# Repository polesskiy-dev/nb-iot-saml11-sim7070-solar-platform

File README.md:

# NB IoT platform

### Based on:
* MCU: Microchip SAML11
* GSM, GPS: SIMCom SIM7070
* Power: 2V Solar panel or DC 5V, MPPT harvester, 1xLiFePO4 18650 

### Hardware features:
* Sensors IN: 
  * 2xPulse, 3V3-48V tolerant, optocouple galvanic isolation. Supports NPN, PNP
  * 1xADC, 1V2-48V tolerant
  * 2x4 wires: USART, LIN client, I2C client/host, SPI client/host, RS485 (3V3), 3V3-5V tolerant, buffered
* Sensors power OUT: 3V3, 12V or self-powered
* Power: 1V5-2V5 Solar MPPT Harvester or DC 5V, LiFePO4/Li-ion charger, reverse polarity protection
* [ ] power consumption values plot

### Software features:
* [ ] AWS integration
* [ ] MQTTs
* [ ] I2C BME280 temperature/humidity/pressure sensor support

### Schematics:

### Board:

### Enclosure:
Gainta G113

### BOM:
[Interactive BOM](https://polesskiy-dev.github.io/nb-iot-saml11-sim7070-solar-platform/bom/ibom.html)

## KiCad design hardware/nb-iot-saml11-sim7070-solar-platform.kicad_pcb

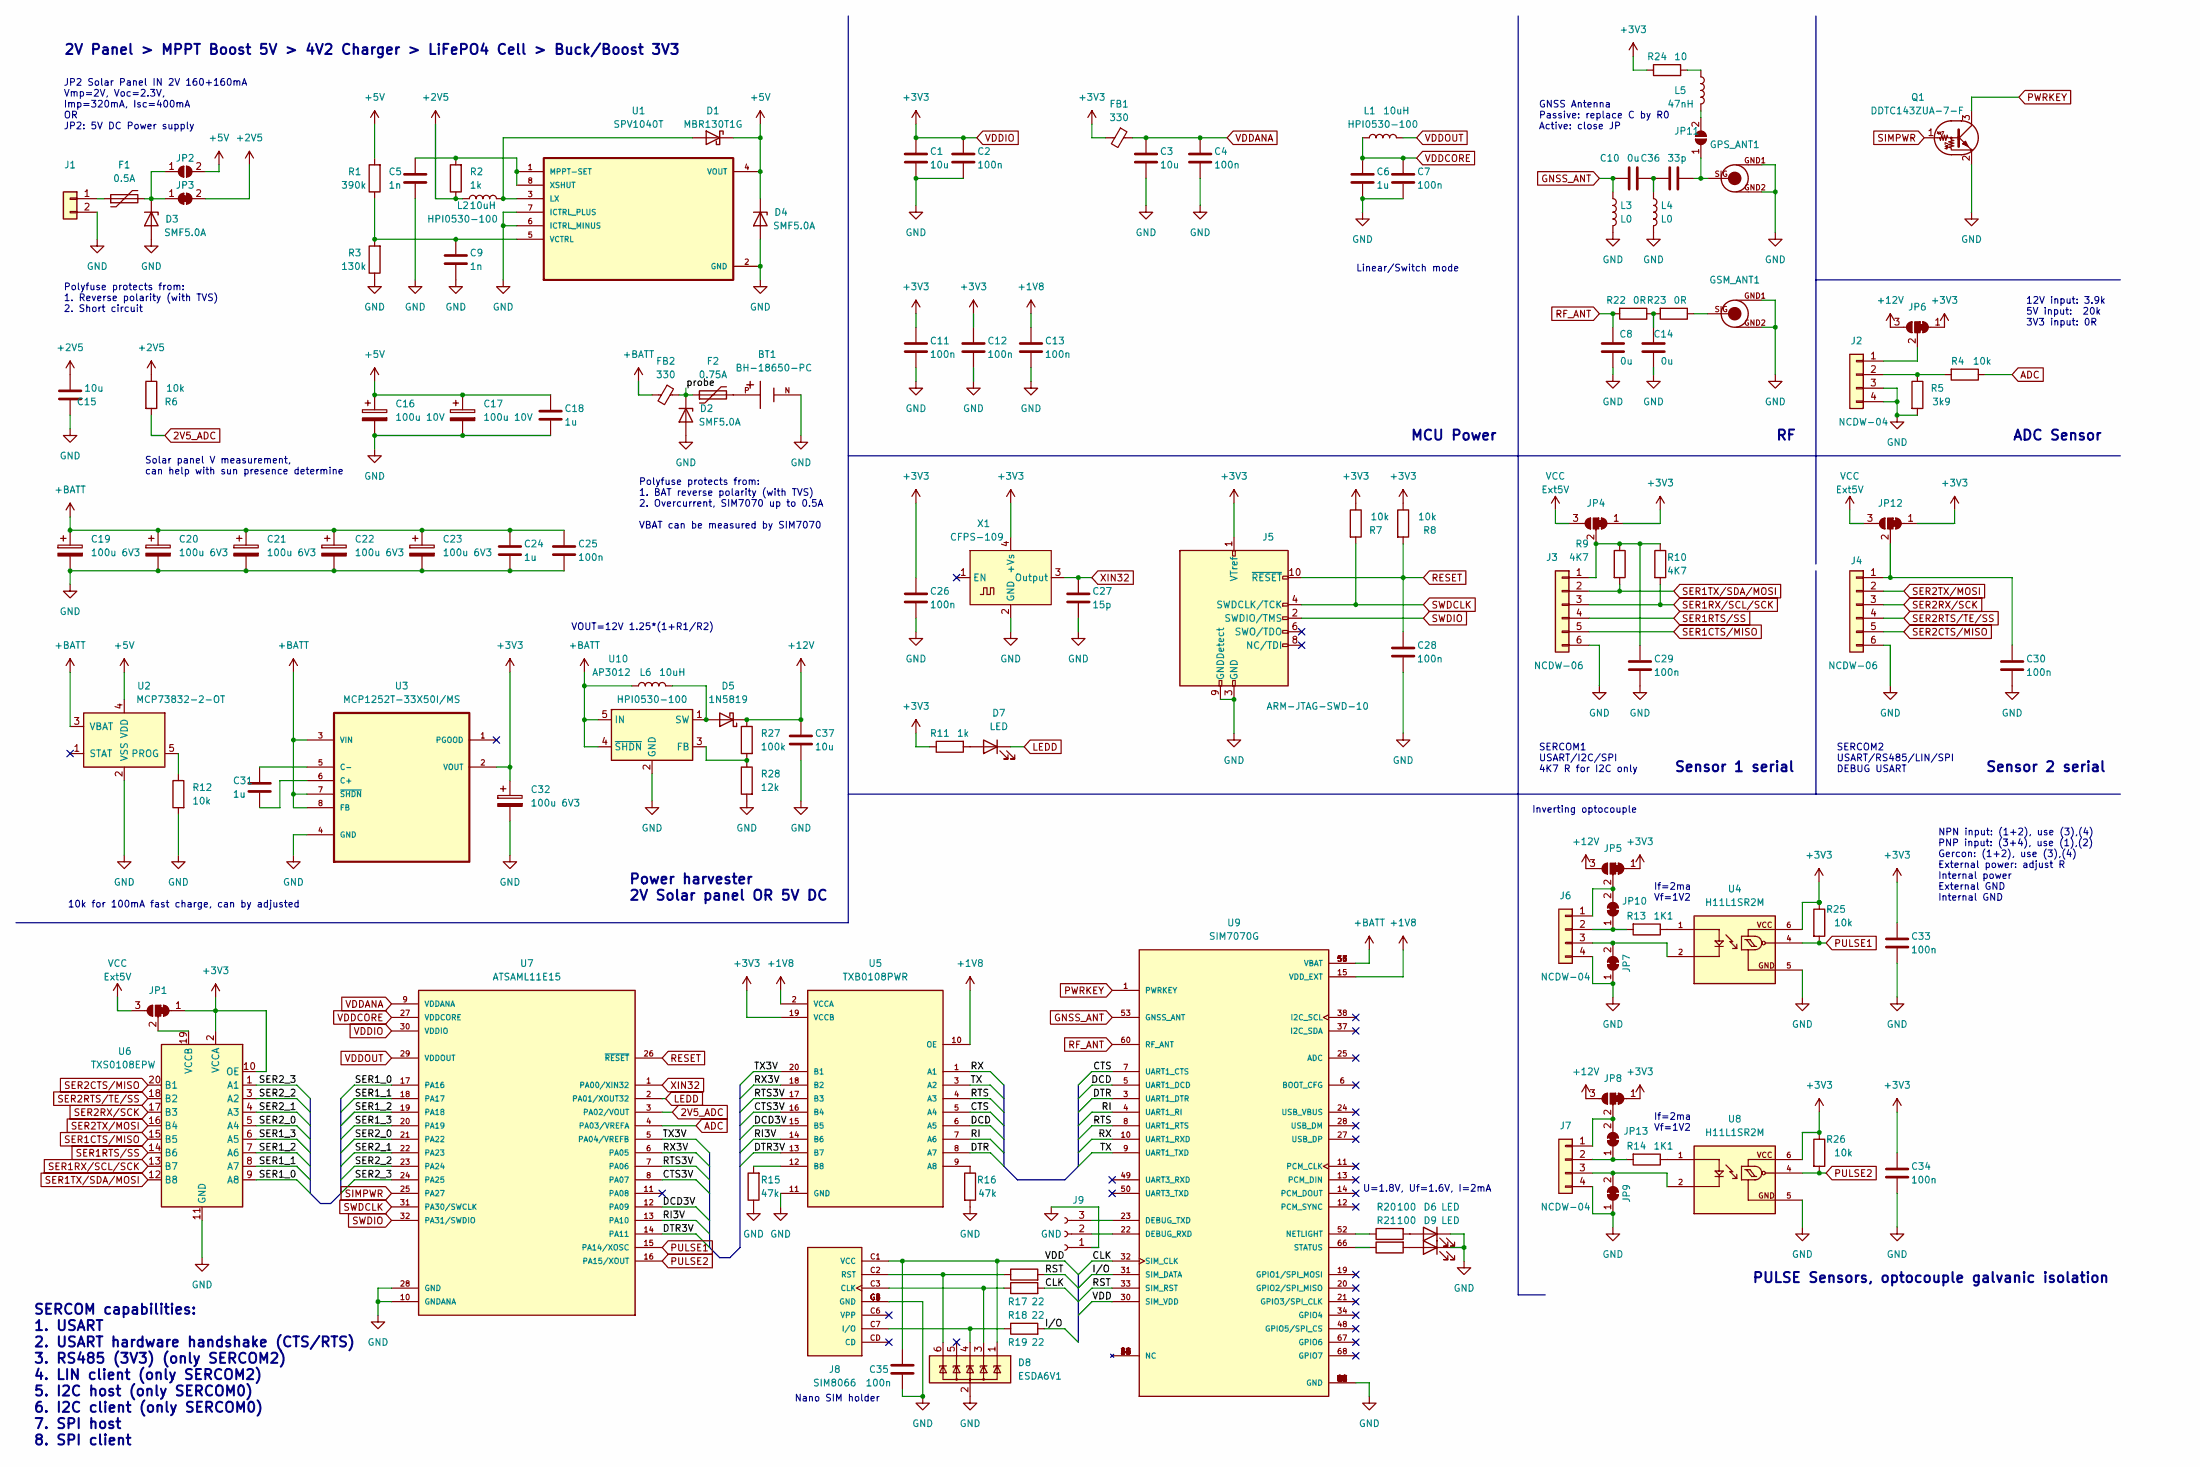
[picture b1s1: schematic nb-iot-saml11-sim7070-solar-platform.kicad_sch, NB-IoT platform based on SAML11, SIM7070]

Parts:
BT1: BH-18650-PC; BAT_BH-18650-PC; PARTREV 05/17/19
C1, C3, C15, C37: 10u; C_0805_2012Metric_Pad1.18x1.45mm_HandSolder
C2, C4, C7, C11, C12, C13, C25, C26, C28, C29, C30, C33, C34, C35: 100n; C_0805_2012Metric_Pad1.18x1.45mm_HandSolder
C5, C9: 1n; C_0805_2012Metric_Pad1.18x1.45mm_HandSolder
C6, C18, C24, C31: 1u; C_0805_2012Metric_Pad1.18x1.45mm_HandSolder
C8, C10, C14: 0u; C_0603_1608Metric_Pad1.08x0.95mm_HandSolder
C16, C17: 100u 10V; CP_EIA-7343-31_Kemet-D_Pad2.25x2.55mm_HandSolder; PARTNUMBER T491D107K010AT
C19, C20, C21, C22, C23, C32: 100u 6V3; CP_EIA-3528-21_Kemet-B_Pad1.50x2.35mm_HandSolder; PARTNUMBER TAJB107K006RNJ
C27: 15p; C_0805_2012Metric_Pad1.18x1.45mm_HandSolder
C36: 33p; C_0603_1608Metric_Pad1.08x0.95mm_HandSolder
D1: D_Schottky; D_SOD-123; PARTNUMBER MBR130T1G
D2, D3, D4: D_Zener; D_SOD-123; PARTNUMBER SMF5.0A
D5: 1N5819; D_SOD-123
D6, D7, D9: LED; LED_0805_2012Metric_Pad1.15x1.40mm_HandSolder
D8: ESDA6V1; SOT-23-6
F1: 0.5A; Fuse_1206_3216Metric_Pad1.42x1.75mm_HandSolder; PARTNUMBER SMD1206P050TF
F2: 0.75A; Fuse_2920_7451Metric_Pad2.10x5.45mm_HandSolder; PARTNUMBER 0ZCF0075FF2C
FB1, FB2: 330; R_0805_2012Metric_Pad1.20x1.40mm_HandSolder
GPS_ANT1: U.FL-R-SMT-1; GHI-CONNECTORS_U.FL-R-SMT-1
GSM_ANT1: U.FL-R-SMT-1; GHI-CONNECTORS_U.FL-R-SMT-1
J1: Conn_01x02; Molex_SL_171971-0002_1x02_P2.54mm_Vertical
J2, J6, J7: NCDW-04; Molex_SL_171971-0004_1x04_P2.54mm_Vertical
J3, J4: NCDW-06; Molex_SL_171971-0006_1x06_P2.54mm_Vertical
J5: ARM-JTAG-SWD-10; PinHeader_2x05_P2.54mm_Vertical
J8: SIM8066; GCT_SIM8066-6-1-14-01-A_REVA; PARTREV REVA
J9: Conn_01x03_Female; PinHeader_1x03_P2.54mm_Vertical
JP1, JP4, JP5, JP6, JP8, JP12: SolderJumper_3_Bridged12; SolderJumper-3_P1.3mm_Bridged12_RoundedPad1.0x1.5mm_NumberL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
JP2, JP11: SolderJumper_2_Open; SolderJumper-2_P1.3mm_Open_RoundedPad1.0x1.5mm
JP3, JP7, JP9, JP10, JP13: SolderJumper_2_Bridged; SolderJumper-2_P1.3mm_Bridged_RoundedPad1.0x1.5mm
L1, L2, L6: 10uH; L_Taiyo-Yuden_MD-5050; PARTNUMBER HPI0530-100
L3, L4: L0; L_0603_1608Metric_Pad1.05x0.95mm_HandSolder
L5: 47nH; L_0603_1608Metric_Pad1.05x0.95mm_HandSolder
Q1: DDTC143ZUA-7-F; SOT-323_SC-70_Handsoldering
R1: 390k; R_0805_2012Metric_Pad1.20x1.40mm_HandSolder
R2, R11: 1k; R_0805_2012Metric_Pad1.20x1.40mm_HandSolder
R3: 130k; R_0805_2012Metric_Pad1.20x1.40mm_HandSolder
R4, R6, R7, R8, R12, R25, R26: 10k; R_0805_2012Metric_Pad1.20x1.40mm_HandSolder
R5: 3k9; R_0805_2012Metric_Pad1.20x1.40mm_HandSolder
R9, R10: 4K7; R_0805_2012Metric_Pad1.20x1.40mm_HandSolder
R13, R14: 1K1; R_0805_2012Metric_Pad1.20x1.40mm_HandSolder
R15, R16: 47k; R_0805_2012Metric_Pad1.20x1.40mm_HandSolder
R17, R18, R19: 22; R_0805_2012Metric_Pad1.20x1.40mm_HandSolder
R20, R21: 100; R_0805_2012Metric_Pad1.20x1.40mm_HandSolder
R22, R23: 0R; R_0603_1608Metric_Pad0.98x0.95mm_HandSolder
R24: 10; R_0805_2012Metric_Pad1.20x1.40mm_HandSolder
R27: 100k; R_0805_2012Metric_Pad1.20x1.40mm_HandSolder
R28: 12k; R_0805_2012Metric_Pad1.20x1.40mm_HandSolder
U1: SPV1040T; TSSOP-8_4.4x3mm_P0.65mm; PARTREV 7
U2: MCP73832-2-OT; SOT-23-5_HandSoldering
U3: MCP1252T-33X50I/MS; MSOP-8_3x3mm_P0.65mm; MPN MCP1252T-33X50I/MS
U4, U8: H11L1SR2M; IC_H11L1SR2M; PARTREV 3
U5: TXB0108PWR; TSSOP-20_4.4x6.5mm_P0.65mm; PARTREV H
U6: TXS0108EPW; TSSOP-20_4.4x6.5mm_P0.65mm
U7: ATSAML11E15; TQFP-32_7x7mm_P0.8mm; PARTREV G
U9: SIM7070G; MODULE_SIM7070G; PARTREV V1.03
U10: AP3012; SOT-23-5
X1: CFPS-109

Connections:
2V5_ADC: R6.2, U7.3 (PA02/VOUT)
+1V8: C13.1, U5.2 (VCCA), U5.10 (OE), U9.15 (VDD_EXT)
+2V5: C15.2, JP3.2 (B), L2.1, R2.1, R6.1
+5V: C16.1, C17.1, C18.1, D1.1 (K), D4.1 (K), JP2.2 (B), R1.2, U1.4 (VOUT), U2.4 (VDD)
+12V: C37.1, D5.1 (K), JP5.3 (B), JP6.3 (B), JP8.3 (B), R27.1
+BATT: C19.1, C20.1, C21.1, C22.1, C23.1, C24.1, C25.1, FB2.2, L6.1, U2.3 (VBAT), U3.3 (VIN), U3.7 (~SHDN), U3.8 (FB), U9.55 (VBAT), U9.56 (VBAT), U9.57 (VBAT), U10.4 (~SHDN), U10.5 (IN)
/CLK: R18.2, U9.32 (SIM_CLK)
/CTS: U5.5 (A4), U9.7 (UART1_CTS)
/CTS3V: U5.16 (B4), U7.8 (PA07)
/DCD: U5.6 (A5), U9.5 (UART1_DCD)
/DCD3V: U5.15 (B5), U7.12 (PA09)
/DTR: U5.8 (A7), U9.3 (UART1_DTR)
/DTR3V: U5.13 (B7), U7.14 (PA11)
/I/O: R19.2, U9.31 (SIM_DATA)
/RI: U5.7 (A6), U9.4 (UART1_RI)
/RI3V: U5.14 (B6), U7.13 (PA10)
/RST: R17.2, U9.33 (SIM_RST)
/RTS: U5.4 (A3), U9.8 (UART1_RTS)
/RTS3V: U5.17 (B3), U7.7 (PA06)
/RX: U5.1 (A1), U9.10 (UART1_RXD)
/RX3V: U5.18 (B2), U7.6 (PA05)
/SER1_0: U6.9 (A8), U7.17 (PA16)
/SER1_1: U6.8 (A7), U7.18 (PA17)
/SER1_2: U6.7 (A6), U7.19 (PA18)
/SER1_3: U6.6 (A5), U7.20 (PA19)
/SER2_0: U6.5 (A4), U7.21 (PA22)
/SER2_1: U6.4 (A3), U7.22 (PA23)
/SER2_2: U6.3 (A2), U7.23 (PA24)
/SER2_3: U6.1 (A1), U7.24 (PA25)
/TX: U5.3 (A2), U9.9 (UART1_TXD)
/TX3V: U5.20 (B1), U7.5 (PA04/VREFB)
/VDD: C35.1, D8.1 (IO1), J8.C1 (VCC), U9.30 (SIM_VDD)
/probe: D2.1 (K), F2.1, FB2.1; also elsewhere on the board
ADC: R4.1, U7.4 (PA03/VREFA)
GND: BT1.N, C1.2, C2.2, C3.2, C4.2, C5.2, C6.2, C7.2, C8.1, C9.2, C11.2, C12.2, C13.2, C14.1, C15.1, C16.2, C17.2, C18.2, C19.2, C20.2, C21.2, C22.2, C23.2, C24.2, C25.2, C26.2, C27.2, C28.2, C29.2, C30.2, C32.2, C33.2, C34.2, C35.2, C37.2, D2.2 (A), D3.2 (A), D4.2 (A), D6.1 (K), D8.2 (GND), D9.1 (K), GPS_ANT1.GND1, GPS_ANT1.GND2, GSM_ANT1.GND1, GSM_ANT1.GND2, J1.2, J2.3, J2.4, J3.6, J4.6, J5.3 (GND), J5.5 (GND), J5.9 (GNDDetect), J6.4, J7.4, J8.C5 (GND), J8.G1 (GND), J8.G2 (GND), J8.G3 (GND), J8.G4 (GND), J9.1, JP7.1 (A), JP9.1 (A), L3.2, L4.2, Q1.2 (E), R3.1, R5.2, R12.2, R15.1, R16.2, R28.2, U1.2 (GND), U1.6 (ICTRL_MINUS), U1.7 (ICTRL_PLUS), U2.2 (VSS), U3.4 (GND), U4.5, U5.11 (GND), U6.11 (GND), U7.10 (GNDANA), U7.28 (GND), U8.5, U9.2 (GND), U9.17 (GND), U9.18 (GND), U9.29 (GND), U9.39 (GND), U9.45 (GND), U9.46 (GND), U9.54 (GND), U9.58 (GND), U9.59 (GND), U9.61 (GND), U9.62 (GND), U9.63 (GND), U9.64 (GND), U9.65 (GND), U10.2 (GND), X1.2 (GND); also elsewhere on the board
GNSS_ANT: C10.2, L3.1, U9.53 (GNSS_ANT)
LEDD: D7.1 (K), U7.2 (PA01/XOUT32)
unnamed: BT1.P, F2.2
unnamed: C5.1, R2.2, U1.1 (MPPT-SET), U1.8 (XSHUT)
unnamed: C9.1, R1.1, R3.2, U1.5 (VCTRL)
unnamed: C10.1, C36.2, L4.1
unnamed: C14.2, R22.1, R23.2
unnamed: C29.1, J3.1, JP4.2 (C), R9.1, R10.1
unnamed: C30.1, J4.1, JP12.2 (C)
unnamed: C31.1, U3.5 (C-)
unnamed: C31.2, U3.6 (C+)
unnamed: C36.1, GPS_ANT1.SIG, JP11.1 (A)
unnamed: D1.2 (A), L2.2, U1.3 (LX)
unnamed: D3.1 (K), F1.2, JP2.1 (A), JP3.1 (A)
unnamed: D5.2 (A), L6.2, U10.1 (SW)
unnamed: D6.2 (A), R20.2
unnamed: D7.2 (A), R11.2
unnamed: D8.3 (IO2), J8.C3 (CLK), R18.1
unnamed: D8.4 (IO3), J8.C7 (I/O), R19.1
unnamed: D8.6 (IO5), J8.C2 (RST), R17.1
unnamed: D9.2 (A), R21.2
unnamed: F1.1, J1.1
unnamed: GSM_ANT1.SIG, R23.1
unnamed: J2.1, JP6.2 (C)
unnamed: J2.2, R4.2, R5.1
unnamed: J6.1, JP5.2 (C), JP10.2 (B)
unnamed: J6.2, JP10.1 (A), R13.2
unnamed: J6.3, JP7.2 (B), U4.2
unnamed: J7.1, JP8.2 (C), JP13.2 (B)
unnamed: J7.2, JP13.1 (A), R14.2
unnamed: J7.3, JP9.2 (B), U8.2
unnamed: J9.2, U9.22 (DEBUG_RXD)
unnamed: J9.3, U9.23 (DEBUG_TXD)
unnamed: JP1.2 (C), U6.19 (VCCB)
unnamed: JP11.2 (B), L5.2
unnamed: L5.1, R24.2
unnamed: R12.1, U2.5 (PROG)
unnamed: R13.1, U4.1
unnamed: R14.1, U8.1
unnamed: R15.2, U5.12 (B8)
unnamed: R16.1, U5.9 (A8)
unnamed: R20.1, U9.52 (NETLIGHT)
unnamed: R21.1, U9.66 (STATUS)
unnamed: R27.2, R28.1, U10.3 (FB)
PULSE1: R25.2, U4.4, U7.15 (PA14/XOSC)
PULSE2: R26.2, U7.16 (PA15/XOUT), U8.4
PWRKEY: Q1.3 (C), U9.1 (PWRKEY)
RESET: C28.1, J5.10 (~RESET), R8.2, U7.26 (~RESET)
RF_ANT: C8.2, R22.2, U9.60 (RF_ANT)
SER1CTS/MISO: J3.5, U6.15 (B5)
SER1RTS/SS: J3.4, U6.14 (B6)
SER1RX/SCL/SCK: J3.3, R10.2, U6.13 (B7)
SER1TX/SDA/MOSI: J3.2, R9.2, U6.12 (B8)
SER2CTS/MISO: J4.5, U6.20 (B1)
SER2RTS/TE/SS: J4.4, U6.18 (B2)
SER2RX/SCK: J4.3, U6.17 (B3)
SER2TX/MOSI: J4.2, U6.16 (B4)
SIMPWR: Q1.1 (B), U7.25 (PA27)
SWDCLK: J5.4 (SWDCLK/TCK), R7.2, U7.31 (PA30/SWCLK)
SWDIO: J5.2 (SWDIO/TMS), U7.32 (PA31/SWDIO)
VCC: JP1.3 (B), JP4.3 (B), JP12.3 (B)
VDDANA: C3.1, C4.1, FB1.1, U7.9 (VDDANA)
VDDCORE: C6.1, C7.1, L1.1, U7.27 (VDDCORE)
VDDIO: C1.1, C2.1, C11.1, C12.1, C26.1, C32.1, C33.1, C34.1, FB1.2, J5.1 (VTref), JP1.1 (A), JP4.1 (A), JP5.1 (A), JP6.1 (A), JP8.1 (A), JP12.1 (A), R7.1, R8.1, R11.1, R24.1, R25.1, R26.1, U3.2 (VOUT), U4.6, U5.19 (VCCB), U6.2 (VCCA), U6.10 (OE), U7.30 (VDDIO), U8.6, X1.4 (+Vs)
VDDOUT: L1.2, U7.29 (VDDOUT)
XIN32: C27.1, U7.1 (PA00/XIN32), X1.3 (Output)

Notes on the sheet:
If=2ma Vf=1V2
ADC Sensor
Polyfuse protects from: 1. BAT reverse polarity (with TVS) 2. Overcurrent, SIM7070 up to 0.5A VBAT can be measured by SIM7070
GNSS Antenna Passive: replace C by R0 Active: close JP
10k for 100mA fast charge, can by adjusted
U=1.8V, Uf=1.6V, I=2mA
Power harvester 2V Solar panel OR 5V DC
PULSE Sensors, optocouple galvanic isolation
Sensor 1 serial
MCU Power
Linear/Switch mode
12V input: 3.9k 5V input: 20k 3V3 input: 0R
VOUT=12V 1.25*(1+R1/R2)
2V Panel > MPPT Boost 5V > 4V2 Charger > LiFePO4 Cell > Buck/Boost 3V3
SERCOM1 USART/I2C/SPI 4K7 R for I2C only
SERCOM capabilities: 1. USART 2. USART hardware handshake (CTS/RTS) 3. RS485 (3V3) (only SERCOM2) 4. LIN client (only SERCOM2) 5. I2C host (only SERCOM0) 6. I2C client (only SERCOM0) 7. SPI host 8. SPI client
SERCOM2 USART/RS485/LIN/SPI DEBUG USART
Nano SIM holder
JP2 Solar Panel IN 2V 160+160mA Vmp=2V, Voc=2.3V, Imp=320mA, Isc=400mA OR JP2: 5V DC Power supply
Polyfuse protects from: 1. Reverse polarity (with TVS) 2. Short circuit
NPN input: (1+2), use (3),(4) PNP input: (3+4), use (1),(2) Gercon: (1+2), use (3),(4) External power: adjust R Internal power External GND Internal GND
Sensor 2 serial
Inverting optocouple
Solar panel V measurement, can help with sun presence determine

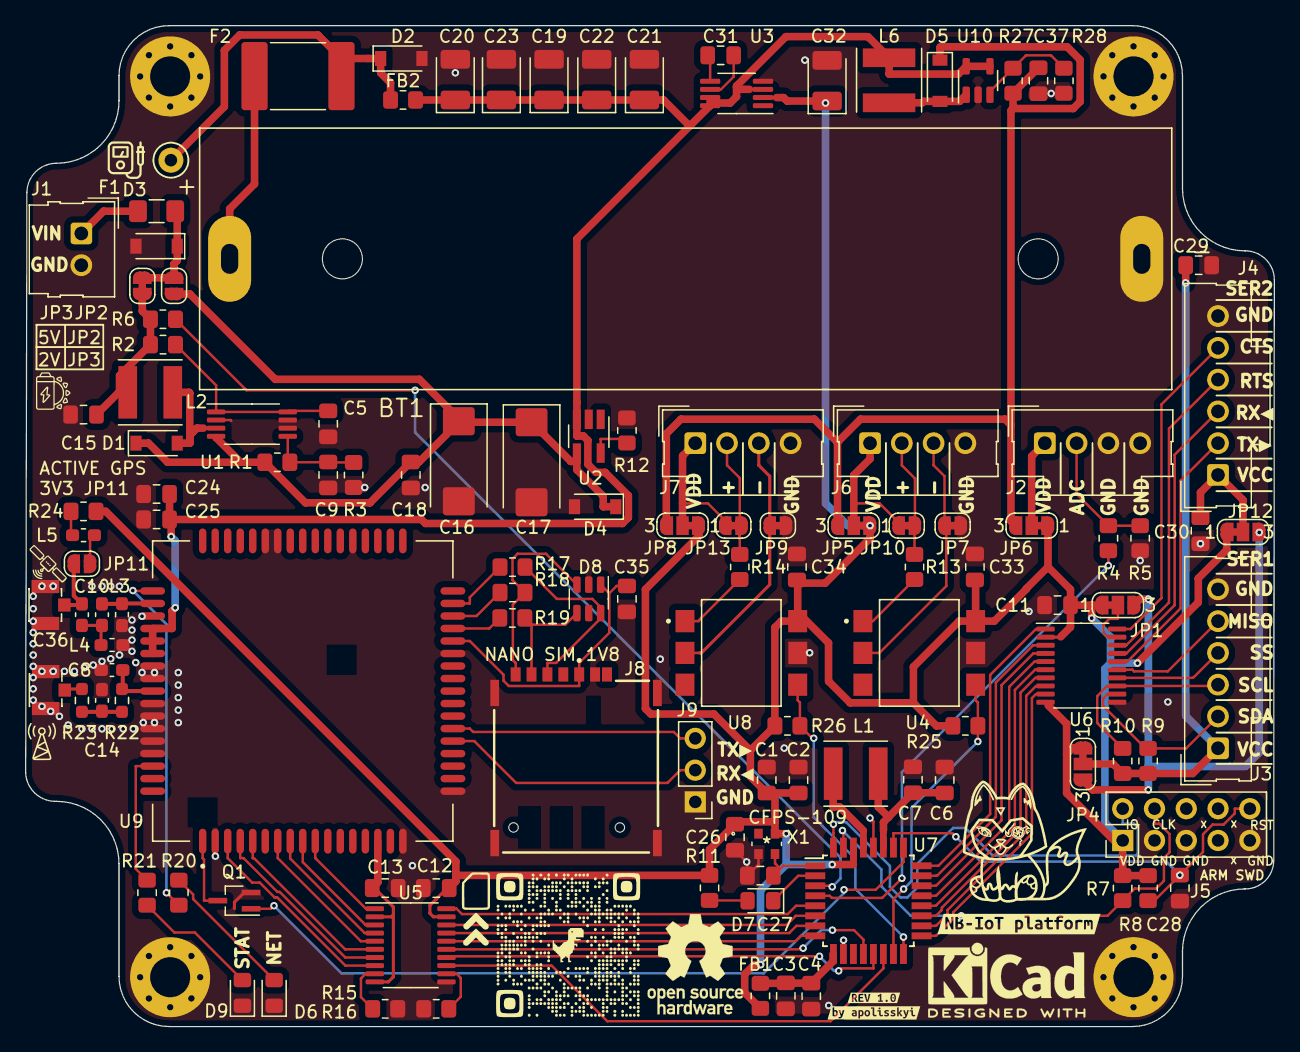
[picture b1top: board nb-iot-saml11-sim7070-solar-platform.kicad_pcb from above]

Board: 2 copper layers, 99.8 x 80.0 mm, 140 parts (0 on the bottom side), 101 nets.

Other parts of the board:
G2, G3, G4, G5, G6, G7, G8, G100: LOGO
REF0: TestPoint_Keystone_5000-5004_Miniature
REF1: OSHW-Logo_7.5x8mm_SilkScreen
REF2: KiCad-Logo2_5mm_SilkScreen
REF6, REF6#2, REF6#3, REF6#4: MountingHole_3.2mm_M3_Pad_Via
kibuzzard-63309E1C: G***; kibuzzard-63309E1C
kibuzzard-6330987C: G***; kibuzzard-6330987C
kibuzzard-63309844: G***; kibuzzard-63309844
kibuzzard-63309884: G***; kibuzzard-63309884

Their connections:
/probe: REF0.1; also elsewhere on the board
GND: REF6.1, REF6#2.1, REF6#3.1, REF6#4.1; also elsewhere on the board

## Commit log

2022-09-29 start adding docs
2022-09-29 trying to add ibom
2022-09-29 add BOM
2022-09-29 docs: update images position
2022-10-02 deploy on gh-pages ibom

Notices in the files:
parts and their libraries:
Copyright 2021 Accelerated Designs. All rights reserved.
